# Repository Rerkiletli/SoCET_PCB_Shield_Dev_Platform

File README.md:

# SoCET_PCB_Shield_Dev_Platform
GPS Shield Using the Ublox NEO-M8Q-01A. Allows user to use USB-C, UART, I2C, or SPI, and allows user to switch between onboard antenna or external antenna.

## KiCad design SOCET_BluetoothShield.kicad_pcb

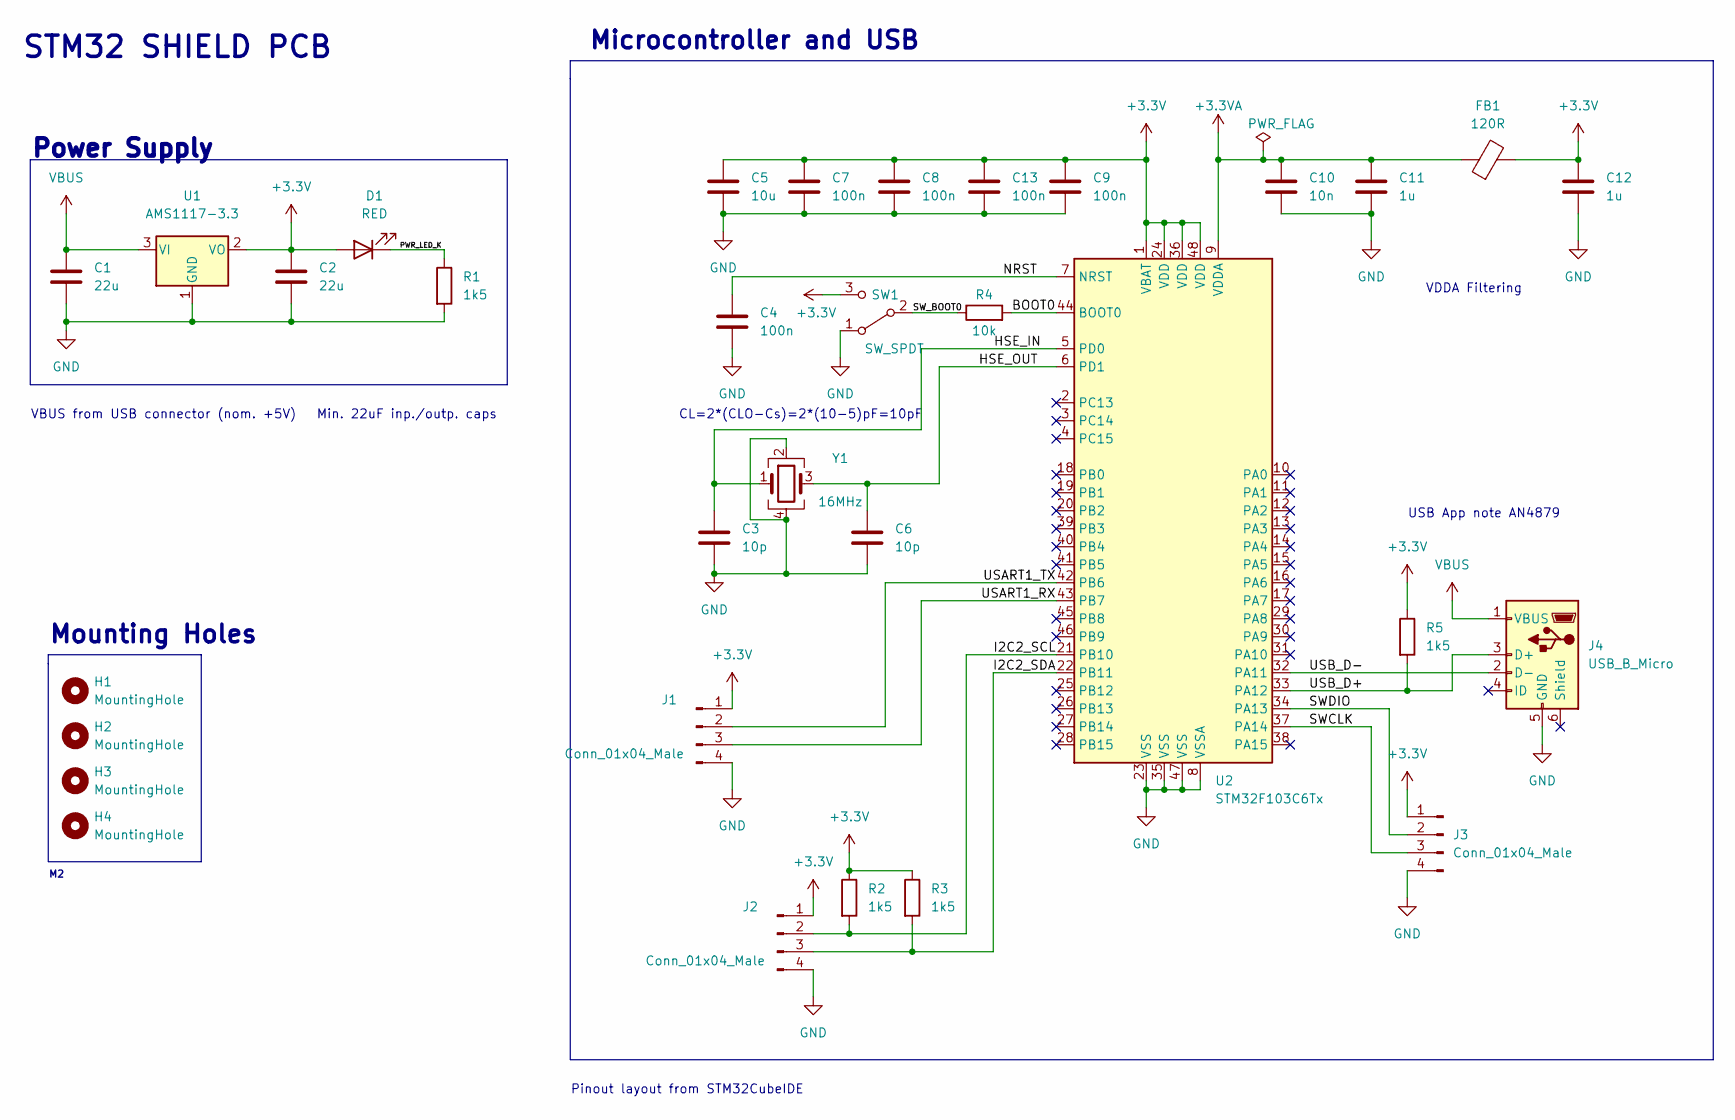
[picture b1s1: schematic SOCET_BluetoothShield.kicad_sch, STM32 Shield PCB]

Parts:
C1, C2: 22u; C_0805_2012Metric
C3, C6: 10p; C_0402_1005Metric
C4, C7, C8, C9, C13: 100n; C_0402_1005Metric
C5: 10u; C_0603_1608Metric
C10: 10n; C_0402_1005Metric
C11, C12: 1u; C_0402_1005Metric
D1: RED; LED_0603_1608Metric
FB1: 120R; L_0603_1608Metric
H1, H2, H3, H4: MountingHole; MountingHole_2.2mm_M2
J1, J2, J3: Conn_01x04_Male; PinHeader_1x04_P2.54mm_Vertical
J4: USB_B_Micro; USB_Micro-B_Wuerth_629105150521
R1, R2, R3, R5: 1k5; R_0402_1005Metric
R4: 10k; R_0402_1005Metric
SW1: SW_SPDT; SW_SPDT_PCM12
U1: AMS1117-3.3; SOT-223-3_TabPin2
U2: STM32F103C6Tx; LQFP-48_7x7mm_P0.5mm
Y1: 16MHz; Crystal_SMD_3225-4Pin_3.2x2.5mm

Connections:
+3.3V: C2.1, C5.1, C7.1, C8.1, C9.1, C12.1, C13.1, D1.2 (A), FB1.2, J1.1, J2.1, J3.1, R2.1, R3.1, R5.1, SW1.3 (C), U1.2 (VO), U2.1 (VBAT), U2.24 (VDD), U2.36 (VDD), U2.48 (VDD)
+3.3VA: C10.1, C11.1, FB1.1, U2.9 (VDDA)
/BOOT0: R4.2, U2.44 (BOOT0)
/HSE_IN: C3.1, U2.5 (PD0), Y1.1
/HSE_OUT: C6.1, U2.6 (PD1), Y1.3
/I2C2_SCL: J2.2, R2.2, U2.21 (PB10)
/I2C2_SDA: J2.3, R3.2, U2.22 (PB11)
/NRST: C4.1, U2.7 (NRST)
/PWR_LED_K: D1.1 (K), R1.1
/SWCLK: J3.3, U2.37 (PA14)
/SWDIO: J3.2, U2.34 (PA13)
/SW_BOOT0: R4.1, SW1.2 (B)
/USART1_RX: J1.3, U2.43 (PB7)
/USART1_TX: J1.2, U2.42 (PB6)
/USB_D+: J4.3 (D+), R5.2, U2.33 (PA12)
/USB_D-: J4.2 (D-), U2.32 (PA11)
GND: C1.2, C2.2, C3.2, C4.2, C5.2, C6.2, C7.2, C8.2, C9.2, C10.2, C11.2, C12.2, C13.2, J1.4, J2.4, J3.4, J4.5 (GND), R1.2, SW1.1 (A), U1.1 (GND), U2.8 (VSSA), U2.23 (VSS), U2.35 (VSS), U2.47 (VSS), Y1.2, Y1.4
VBUS: C1.1, J4.1 (VBUS), U1.3 (VI)

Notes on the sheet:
Microcontroller and USB
Mounting Holes
CL=2*(CLO-Cs)=2*(10-5)pF=10pF
VBUS from USB connector (nom. +5V) Min. 22uF inp./outp. caps
VDDA Filtering
Pinout layout from STM32CubeIDE
USB App note AN4879
Power Supply
STM32 SHIELD PCB

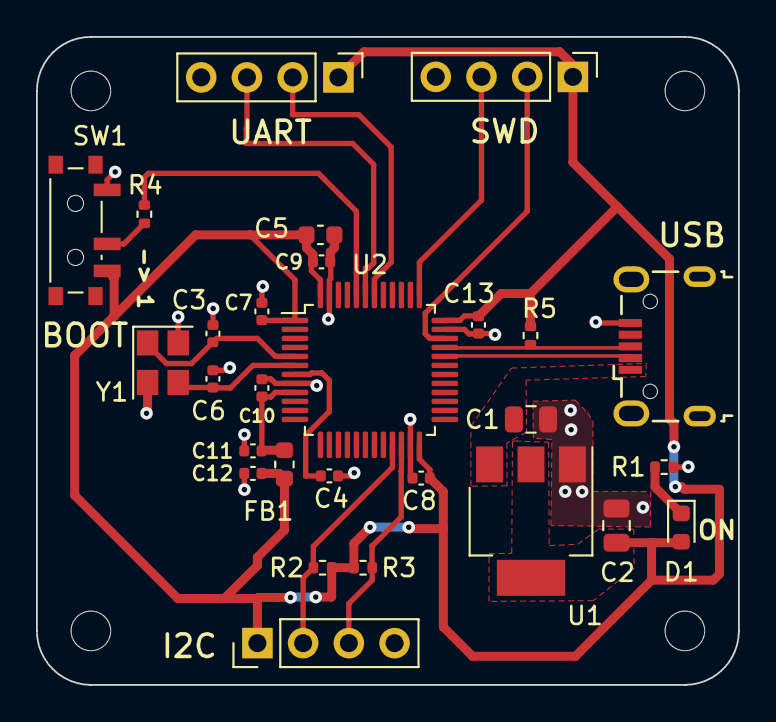
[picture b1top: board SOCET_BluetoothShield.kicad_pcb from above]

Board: 2 copper layers, 39.0 x 36.0 mm, 32 parts (0 on the bottom side), 18 nets.

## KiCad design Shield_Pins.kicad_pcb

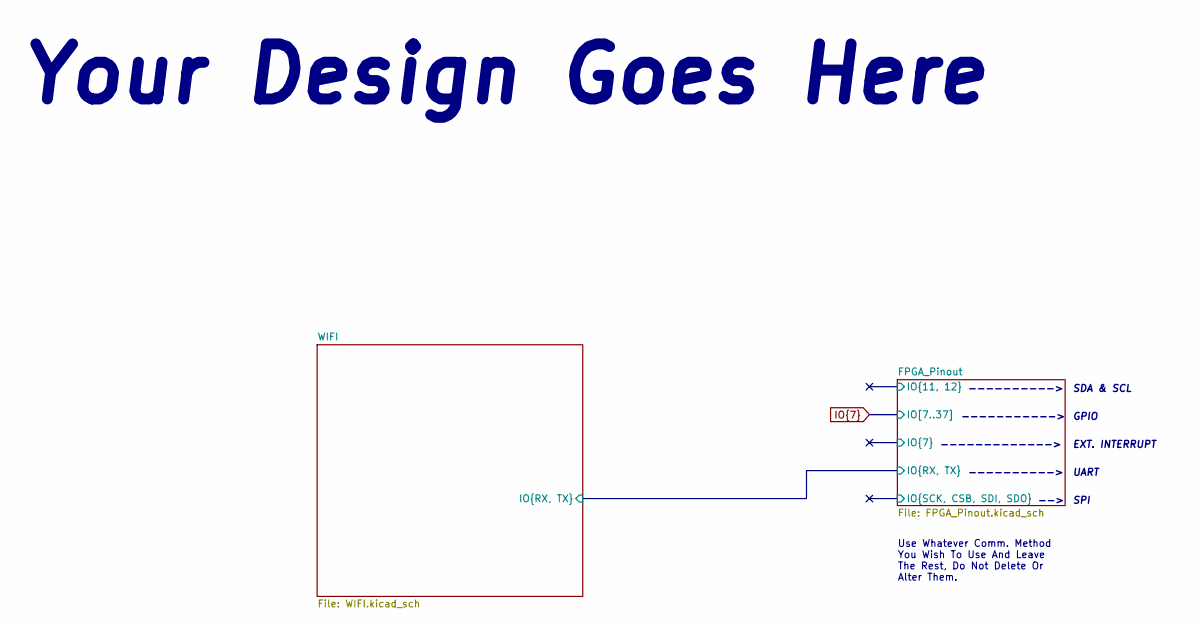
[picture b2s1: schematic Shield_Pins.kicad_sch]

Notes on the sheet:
---------->
UART
GPIO
Your Design Goes Here
Use Whatever Comm. Method You Wish To Use And Leave The Rest, Do Not Delete Or Alter Them.
SDA & SCL
EXT. INTERRUPT
-->
------------->
SPI
----------->

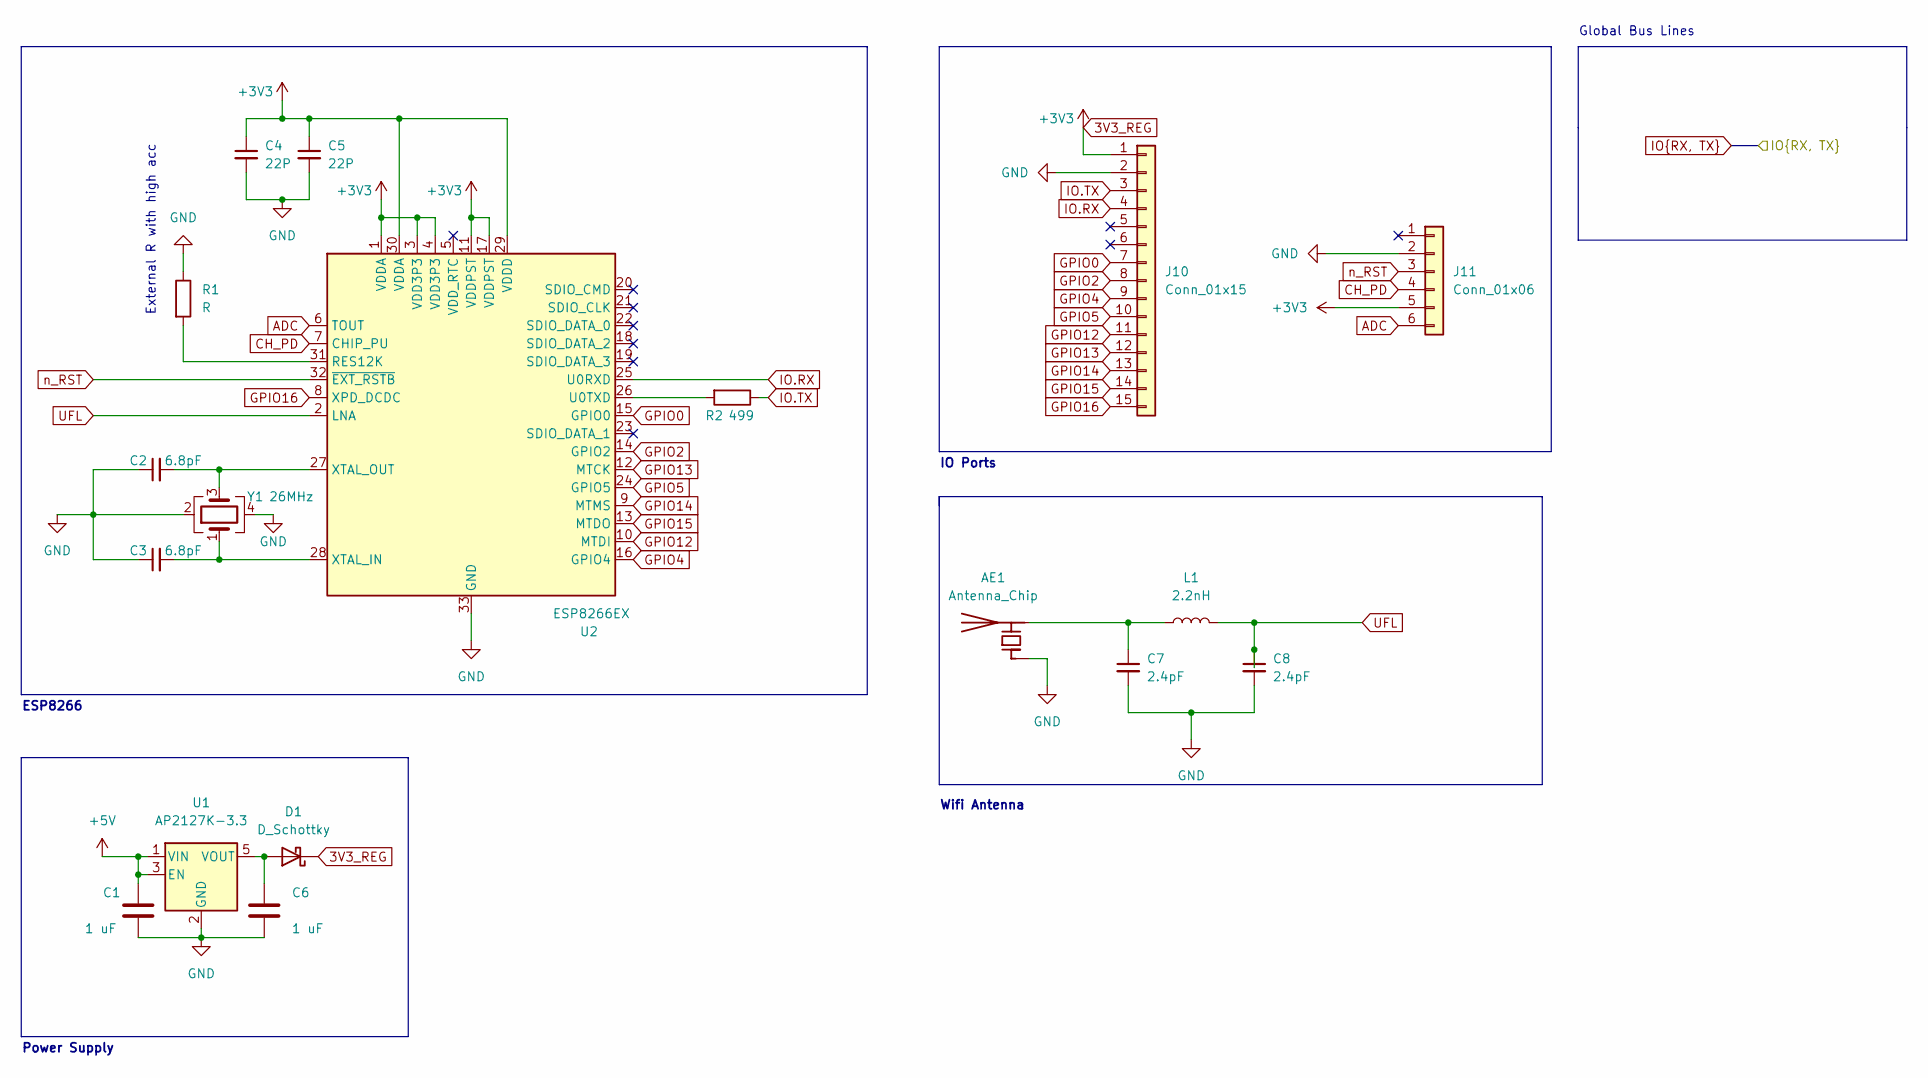
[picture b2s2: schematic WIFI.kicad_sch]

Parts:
AE1: Antenna_Chip; Texas_SWRA117D_2.4GHz_Left
C1, C6: 1 uF; C_1206_3216Metric
C2, C3: 6.8pF; C_1206_3216Metric
C4, C5: 22P; C_1206_3216Metric
C7, C8: 2.4pF; C_1206_3216Metric
D1: D_Schottky; D_1206_3216Metric
J10: Conn_01x15; PinHeader_1x15_P2.00mm_Vertical
J11: Conn_01x06; PinHeader_1x06_P2.00mm_Vertical
L1: 2.2nH; L_0805_2012Metric
R1: R; R_0815_2038Metric
R2: 499; R_0815_2038Metric
U1: AP2127K-3.3; SOT-23-5
U2: ESP8266EX; QFN-32-1EP_5x5mm_P0.5mm_EP3.45x3.45mm
Y1: 26MHz; Crystal_SMD_0603-4Pin_6.0x3.5mm

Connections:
3V3_REG: C4.1, C5.1, D1.1 (K), J10.1, J11.5, U2.1 (VDDA), U2.3 (VDD3P3), U2.4 (VDD3P3), U2.11 (VDDPST), U2.17 (VDDPST), U2.29 (VDDD), U2.30 (VDDA)
+5V: C1.1, U1.1 (VIN), U1.3 (EN); also elsewhere on the board
ADC: J11.6, U2.6 (TOUT)
CH_PD: J11.4, U2.7 (CHIP_PU)
GND: AE1.1 (FEED), C1.2, C2.1, C3.1, C4.2, C5.2, C6.2, C7.2, C8.2, J10.2, J11.2, R1.1, U1.2 (GND), U2.33 (GND), Y1.2, Y1.4; also elsewhere on the board
GPIO0: J10.7, U2.15 (GPIO0)
GPIO2: J10.8, U2.14 (GPIO2)
GPIO4: J10.9, U2.16 (GPIO4)
GPIO5: J10.10, U2.24 (GPIO5)
GPIO12: J10.11, U2.10 (MTDI)
GPIO13: J10.12, U2.12 (MTCK)
GPIO14: J10.13, U2.9 (MTMS)
GPIO15: J10.14, U2.13 (MTDO)
GPIO16: J10.15, U2.8 (XPD_DCDC)
IO.RX: J10.4, U2.25 (U0RXD); also elsewhere on the board
IO.TX: J10.3, R2.1; also elsewhere on the board
unnamed: AE1.2 (PCB_Trace), C7.1, L1.1
unnamed: C2.2, U2.27 (XTAL_OUT), Y1.3
unnamed: C3.2, U2.28 (XTAL_IN), Y1.1
unnamed: C6.1, D1.2 (A), U1.5 (VOUT)
unnamed: R1.2, U2.31 (RES12K)
unnamed: R2.2, U2.26 (U0TXD)
UFL: C8.1, L1.2, U2.2 (LNA)
n_RST: J11.3, U2.32 (~EXT_RSTB)

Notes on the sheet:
Global Bus Lines
ESP8266
External R with high acc
Wifi Antenna
IO Ports
Power Supply

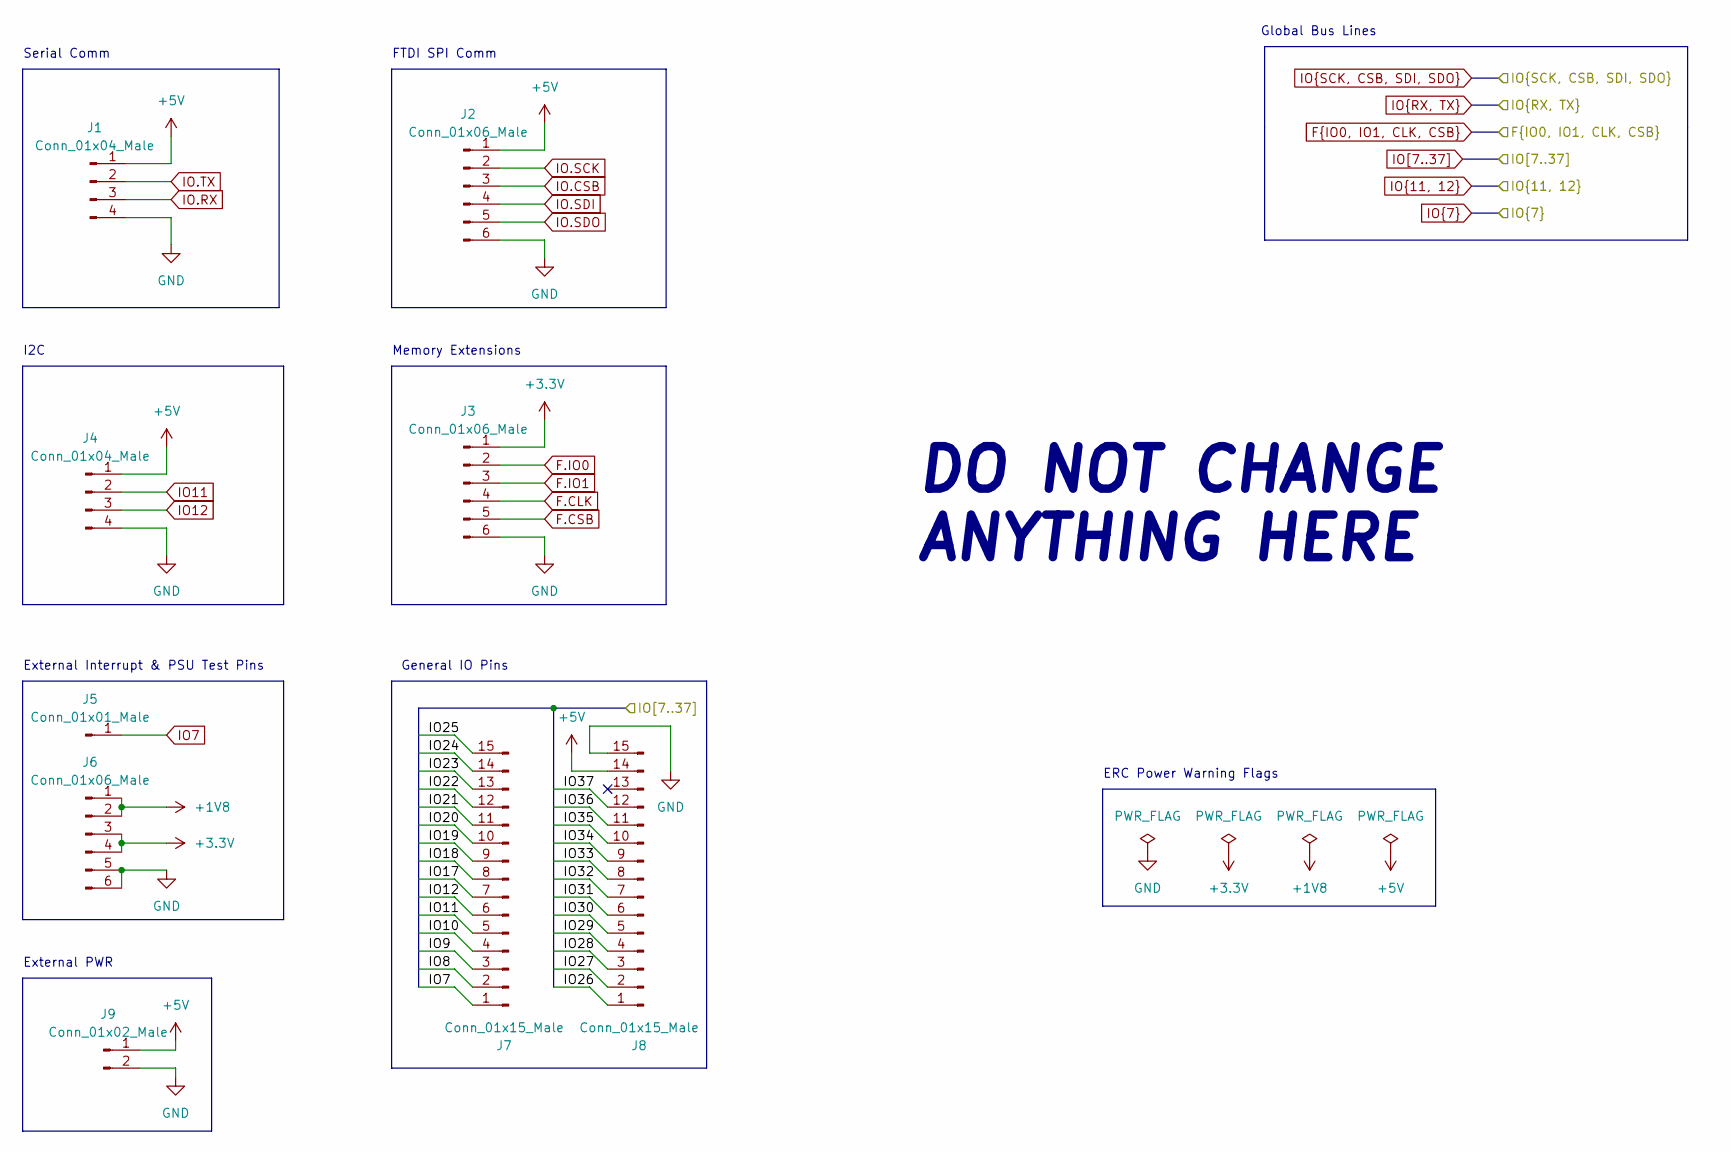
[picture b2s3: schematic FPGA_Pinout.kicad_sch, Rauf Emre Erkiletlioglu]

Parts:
J1, J4: Conn_01x04_Male; PinHeader_1x04_P2.00mm_Vertical
J2, J3, J6: Conn_01x06_Male; PinHeader_1x06_P2.00mm_Vertical
J5: Conn_01x01_Male; PinHeader_1x01_P2.00mm_Vertical
J7, J8: Conn_01x15_Male; PinHeader_1x15_P2.00mm_Vertical
J9: Conn_01x02_Male; PinHeader_1x02_P2.00mm_Vertical

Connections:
+1V8: J6.1, J6.2
+3.3V: J3.1, J6.3, J6.4
+5V: J1.1, J2.1, J4.1, J8.14, J9.1; also elsewhere on the board
F.CLK: J3.4
F.CSB: J3.5
F.IO0: J3.2
F.IO1: J3.3
GND: J1.4, J2.6, J3.6, J4.4, J6.5, J6.6, J8.15, J9.2; also elsewhere on the board
IO7: J5.1, J7.1
IO8: J7.2
IO9: J7.3
IO10: J7.4
IO11: J4.2, J7.5
IO12: J4.3, J7.6
IO17: J7.7
IO18: J7.8
IO19: J7.9
IO20: J7.10
IO21: J7.11
IO22: J7.12
IO23: J7.13
IO24: J7.14
IO25: J7.15
IO26: J8.1
IO27: J8.2
IO28: J8.3
IO29: J8.4
IO30: J8.5
IO31: J8.6
IO32: J8.7
IO33: J8.8
IO34: J8.9
IO35: J8.10
IO36: J8.11
IO37: J8.12
IO.CSB: J2.3
IO.RX: J1.3; also elsewhere on the board
IO.SCK: J2.2
IO.SDI: J2.4
IO.SDO: J2.5
IO.TX: J1.2; also elsewhere on the board

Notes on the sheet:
General IO Pins
External Interrupt & PSU Test Pins
ERC Power Warning Flags
Global Bus Lines
DO NOT CHANGE ANYTHING HERE
Serial Comm
External PWR
Memory Extensions
I2C
FTDI SPI Comm

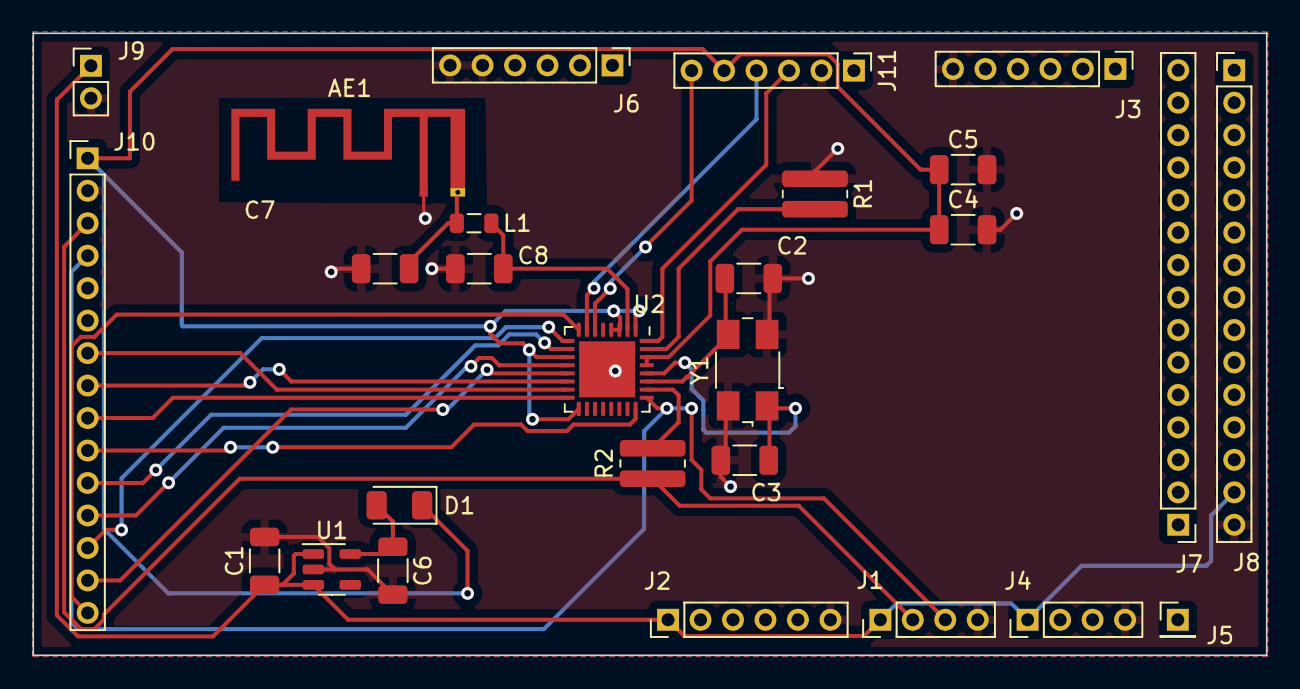
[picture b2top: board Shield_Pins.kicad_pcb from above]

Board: 2 copper layers, 76.0 x 38.3 mm, 27 parts (0 on the bottom side), 29 nets.

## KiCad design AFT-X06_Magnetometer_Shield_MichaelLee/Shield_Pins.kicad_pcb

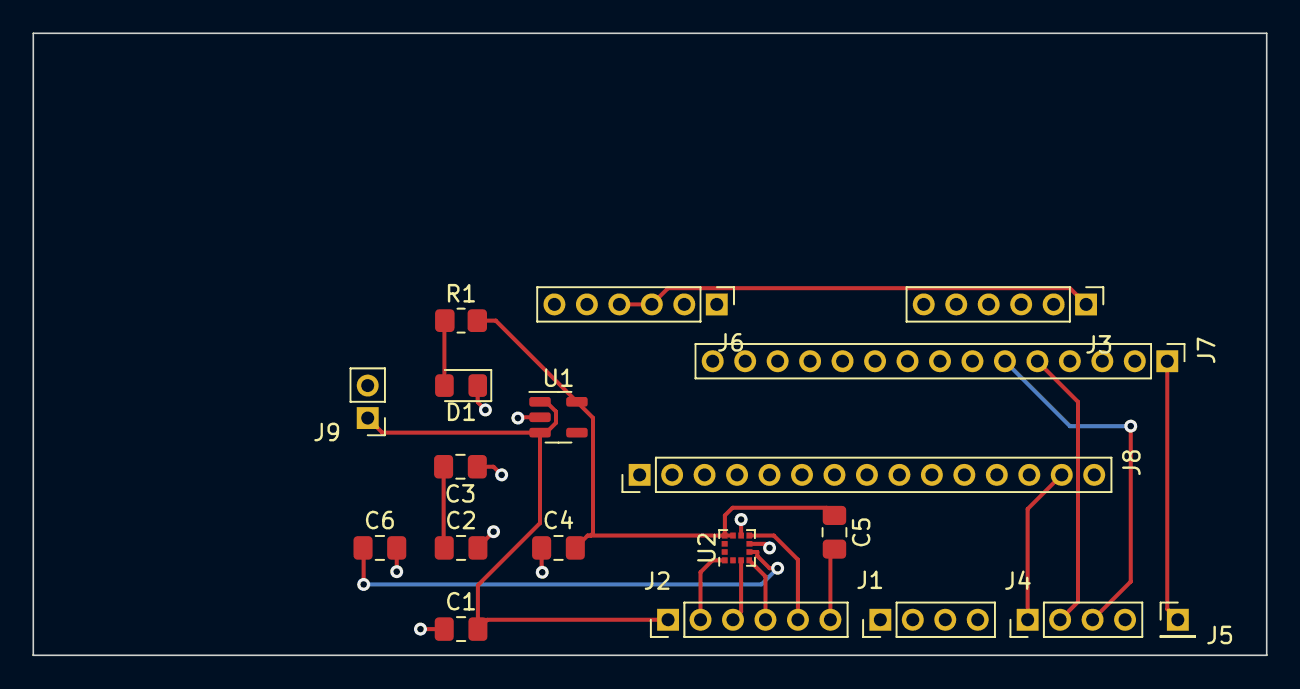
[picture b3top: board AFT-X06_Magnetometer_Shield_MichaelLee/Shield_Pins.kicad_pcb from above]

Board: 2 copper layers, 76.0 x 38.3 mm, 19 parts (0 on the bottom side), 14 nets.

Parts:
C1, C2: 1uF; C_0805_2012Metric_Pad1.18x1.45mm_HandSolder
C3: 10uF; C_0805_2012Metric_Pad1.18x1.45mm_HandSolder
C4, C5: 100nF; C_0805_2012Metric_Pad1.18x1.45mm_HandSolder
C6: 220nF; C_0805_2012Metric_Pad1.18x1.45mm_HandSolder
D1: LED; D_0805_2012Metric_Pad1.15x1.40mm_HandSolder
J1, J4: Conn_01x04_Male; PinHeader_1x04_P2.00mm_Vertical
J2, J3, J6: Conn_01x06_Male; PinHeader_1x06_P2.00mm_Vertical
J5: Conn_01x01_Male; PinHeader_1x01_P2.00mm_Vertical
J7, J8: Conn_01x15_Male; PinHeader_1x15_P2.00mm_Vertical
J9: Conn_01x02_Male; PinHeader_1x02_P2.00mm_Vertical
R1: R; R_0805_2012Metric_Pad1.20x1.40mm_HandSolder
U1: AP2112K-3.3; SOT-23-5
U2: LIS2MDL; LGA-12_2x2mm_P0.5mm

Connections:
+1V8: J6.1, J6.2
+3.3V: J3.1, J6.3, J6.4
+3V3: C2.1, C3.2, C4.2, C5.1, R1.2, U1.5 (VOUT), U2.9 (VDD), U2.10 (VDD_IO)
+5V: C1.2, J1.1, J2.1, J4.1, J8.14, J9.1, U1.1 (VIN), U1.3 (EN)
GND: C1.1, C2.2, C3.1, C4.1, C5.2, C6.2, D1.1 (K), J1.4, J2.6, J3.6, J4.4, J6.5, J6.6, J8.15, J9.2, U1.2 (GND), U2.6 (GND), U2.8 (GND)
IO7: J5.1, J7.1
IO11: J4.2, J7.5
IO12: J4.3, J7.6
IO.CSB: J2.3, U2.3 (CS)
IO.SCK: J2.2, U2.1 (SCL/SPC)
IO.SDI: J2.4, U2.4 (SDA/SDI/SDO)
IO.SDO: J2.5, U2.7 (INT/DRDY/SDO)
unnamed: C6.1, U2.5 (C1)
unnamed: D1.2 (A), R1.1

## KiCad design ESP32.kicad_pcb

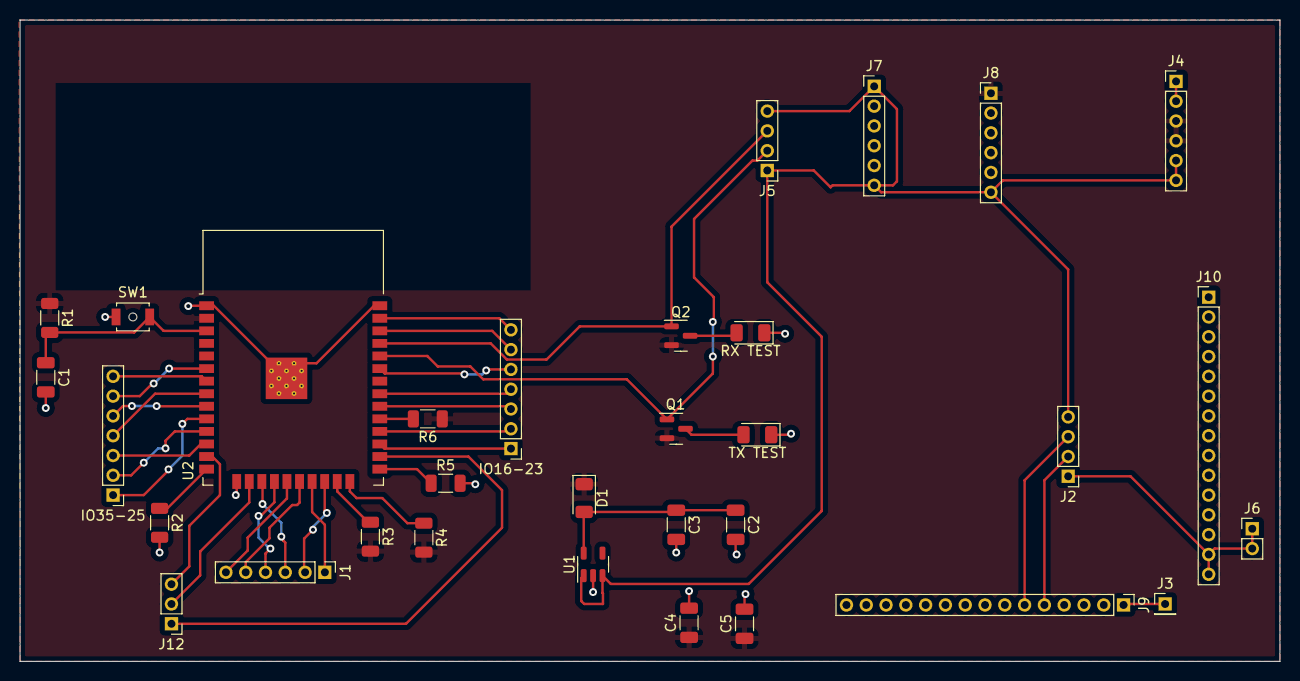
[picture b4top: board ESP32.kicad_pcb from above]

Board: 2 copper layers, 127.3 x 64.8 mm, 32 parts (0 on the bottom side), 41 nets.

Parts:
C1, C2, C3: 10uF; C_1206_3216Metric
C4: 10 uF; C_1206_3216Metric
C5: 100 nF; C_1206_3216Metric
D1: D_Schottky; D_1206_3216Metric
IO16-23, IO35-25: Conn_01x07_Male; PinHeader_1x07_P2.00mm_Vertical
J1, J4, J7, J8: Conn_01x06_Male; PinHeader_1x06_P2.00mm_Vertical
J2, J5: Conn_01x04_Male; PinHeader_1x04_P2.00mm_Vertical
J3: Conn_01x01_Male; PinHeader_1x01_P2.00mm_Vertical
J6: Conn_01x02_Male; PinHeader_1x02_P2.00mm_Vertical
J9, J10: Conn_01x15_Male; PinHeader_1x15_P2.00mm_Vertical
J12: Conn_01x03_Male; PinHeader_1x03_P2.00mm_Vertical
Q1, Q2: BC807; SOT-23
R1, R3, R4, R5, R6: 10K; R_1206_3216Metric
R2: 10k; R_1206_3216Metric
RX TEST: LED; LED_1206_3216Metric
SW1: SW_Push; SW_SPST_B3U-1000P-B
TX TEST: LED; LED_1206_3216Metric
U1: MIC5219-2.5YM5; SOT-23-5
U2: ESP32-WROOM-32

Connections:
+1V8: J4.1, J4.2
+3.3V: C4.1, C5.1, D1.1 (K), J4.3, J4.4, J8.1, Q1.2 (E), Q2.2 (E), R1.1, R3.2, R4.2, R6.1, U2.2 (VDD)
+5V: J2.1, J2.4, J4.5, J4.6, J5.1, J5.4, J6.1, J6.2, J7.1, J7.6, J8.6, J10.14, J10.15, U1.1 (IN), U1.3 (EN)
ESP32_SCK: J1.5, U2.20 (SCK/CLK)
ESP32_SCS: J1.6, U2.19 (SCS/CMD)
ESP32_SD0: J1.1, U2.21 (SDO/SD0)
ESP32_SDI: J1.2, U2.22 (SDI/SD1)
ESP32_SHD: J1.3, U2.17 (SHD/SD2)
ESP32_SWP: J1.4, U2.18 (SWP/SD3)
GND: C1.2, C2.2, C3.2, C4.2, C5.2, R2.2, R5.2, RX TEST.1 (K), SW1.1, TX TEST.1 (K), U1.2 (GND), U2.1 (GND), U2.15 (GND), U2.38 (GND), U2.39 (GND)
IO7: J3.1, J9.1
IO11: J2.2, J9.5
IO12: J2.3, J9.6
IO 4: J12.1, U2.26 (IO4)
IO 13: J12.2, U2.16 (IO13)
IO 14: J12.3, U2.13 (IO14)
IO 16: IO16-23.1, U2.27 (IO16)
IO 17: IO16-23.2, U2.28 (IO17)
IO 18: IO16-23.3, U2.30 (IO18)
IO 19: IO16-23.4, U2.31 (IO19)
IO 21: IO16-23.5, U2.33 (IO21)
IO 22: IO16-23.6, U2.36 (IO22)
IO 23: IO16-23.7, U2.37 (IO23)
IO 25: IO35-25.1, U2.10 (IO25)
IO 26: IO35-25.2, U2.11 (IO26)
IO 27: IO35-25.3, U2.12 (IO27)
IO 32: IO35-25.4, U2.8 (IO32)
IO 33: IO35-25.5, U2.9 (IO33)
IO 34: IO35-25.6, U2.6 (IO34)
IO 35: IO35-25.7, U2.7 (IO35)
IO.RX: J5.3, Q2.1 (B), U2.35 (TXD0/IO1)
IO.TX: J5.2, Q1.1 (B), U2.34 (RXD0/IO3)
unnamed: C1.1, R1.2, SW1.2, U2.3 (EN)
unnamed: C2.1, C3.1, D1.2 (A), U1.5 (OUT)
unnamed: Q1.3 (C), TX TEST.2 (A)
unnamed: Q2.3 (C), RX TEST.2 (A)
unnamed: R4.1, U2.24 (IO2)
unnamed: R5.1, U2.25 (IO0)
unnamed: R6.2, U2.29 (IO5)
unnamed: R2.1, U2.14 (IO12)
unnamed: R3.1, U2.23 (IO15)

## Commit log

2023-02-17 First commit: GPS Shield Schematic Progress
2023-02-17 First Shield Commit
2023-02-18 Init Push
2023-02-18 Vijay
2023-02-19 WiFi Shield
2023-02-20 Complete board (1)
2023-02-22 Complete board (2)
2023-02-27 Update WiFi Shield schematic and create layout
2023-03-01 ishaan
2023-03-01 latestwork
2023-03-02 Add files via upload
    01/02/2023
2023-03-02 Add files via upload
    01/03/2023
2023-03-04 Schematic/Layout update based on feedback
2023-03-05 Fix some minor errors
2023-03-05 Revised Version
2023-05-31 1st push attempt
2023-06-02 Schematics V1 done, still need Pi filter numbers
2023-06-02 shield
2023-06-03 Filter values added
2023-06-03 fixed some erc errors and added decoupling cap
2023-06-03 Day 1 feedback applied
2023-06-03 tried to fix erc errors
2023-06-04 Add files via upload
    minor fixes
2023-06-05 Add files via upload
    Grade V1
2023-06-06 clean up symbols
2023-06-06 design put into new sheet and revised
2023-06-06 cleanup files
2023-06-06 added top and bottom gnd layer
2023-06-06 reset circuit changed to pull down
2023-06-06 simplified power management components
2023-06-09 pcb v1 design done, silkscreen still needs work
2023-09-20 Indrayudh
2023-09-23 Fixed Schematic with LDR, Capacitor Network, and magnetic RJ45. Re-did the PCB layout
2023-09-23 Minor Silkscreen Design fix
2023-09-24 Indrayudh Chowdhury
2023-09-25 Initial schematic
2023-09-25 next commit
2023-09-25 pcb initial
2023-09-28 Revised PCB and Sheet
2023-09-28 Revised schematic. Re-did Board to 2 Layers
2023-10-10 Final Revision
2023-10-10 Fix silkscreen issue
2023-10-16 Finished shield design
2024-03-22 Delete RGBWShield.net
    Push it to the branch, not to the main
